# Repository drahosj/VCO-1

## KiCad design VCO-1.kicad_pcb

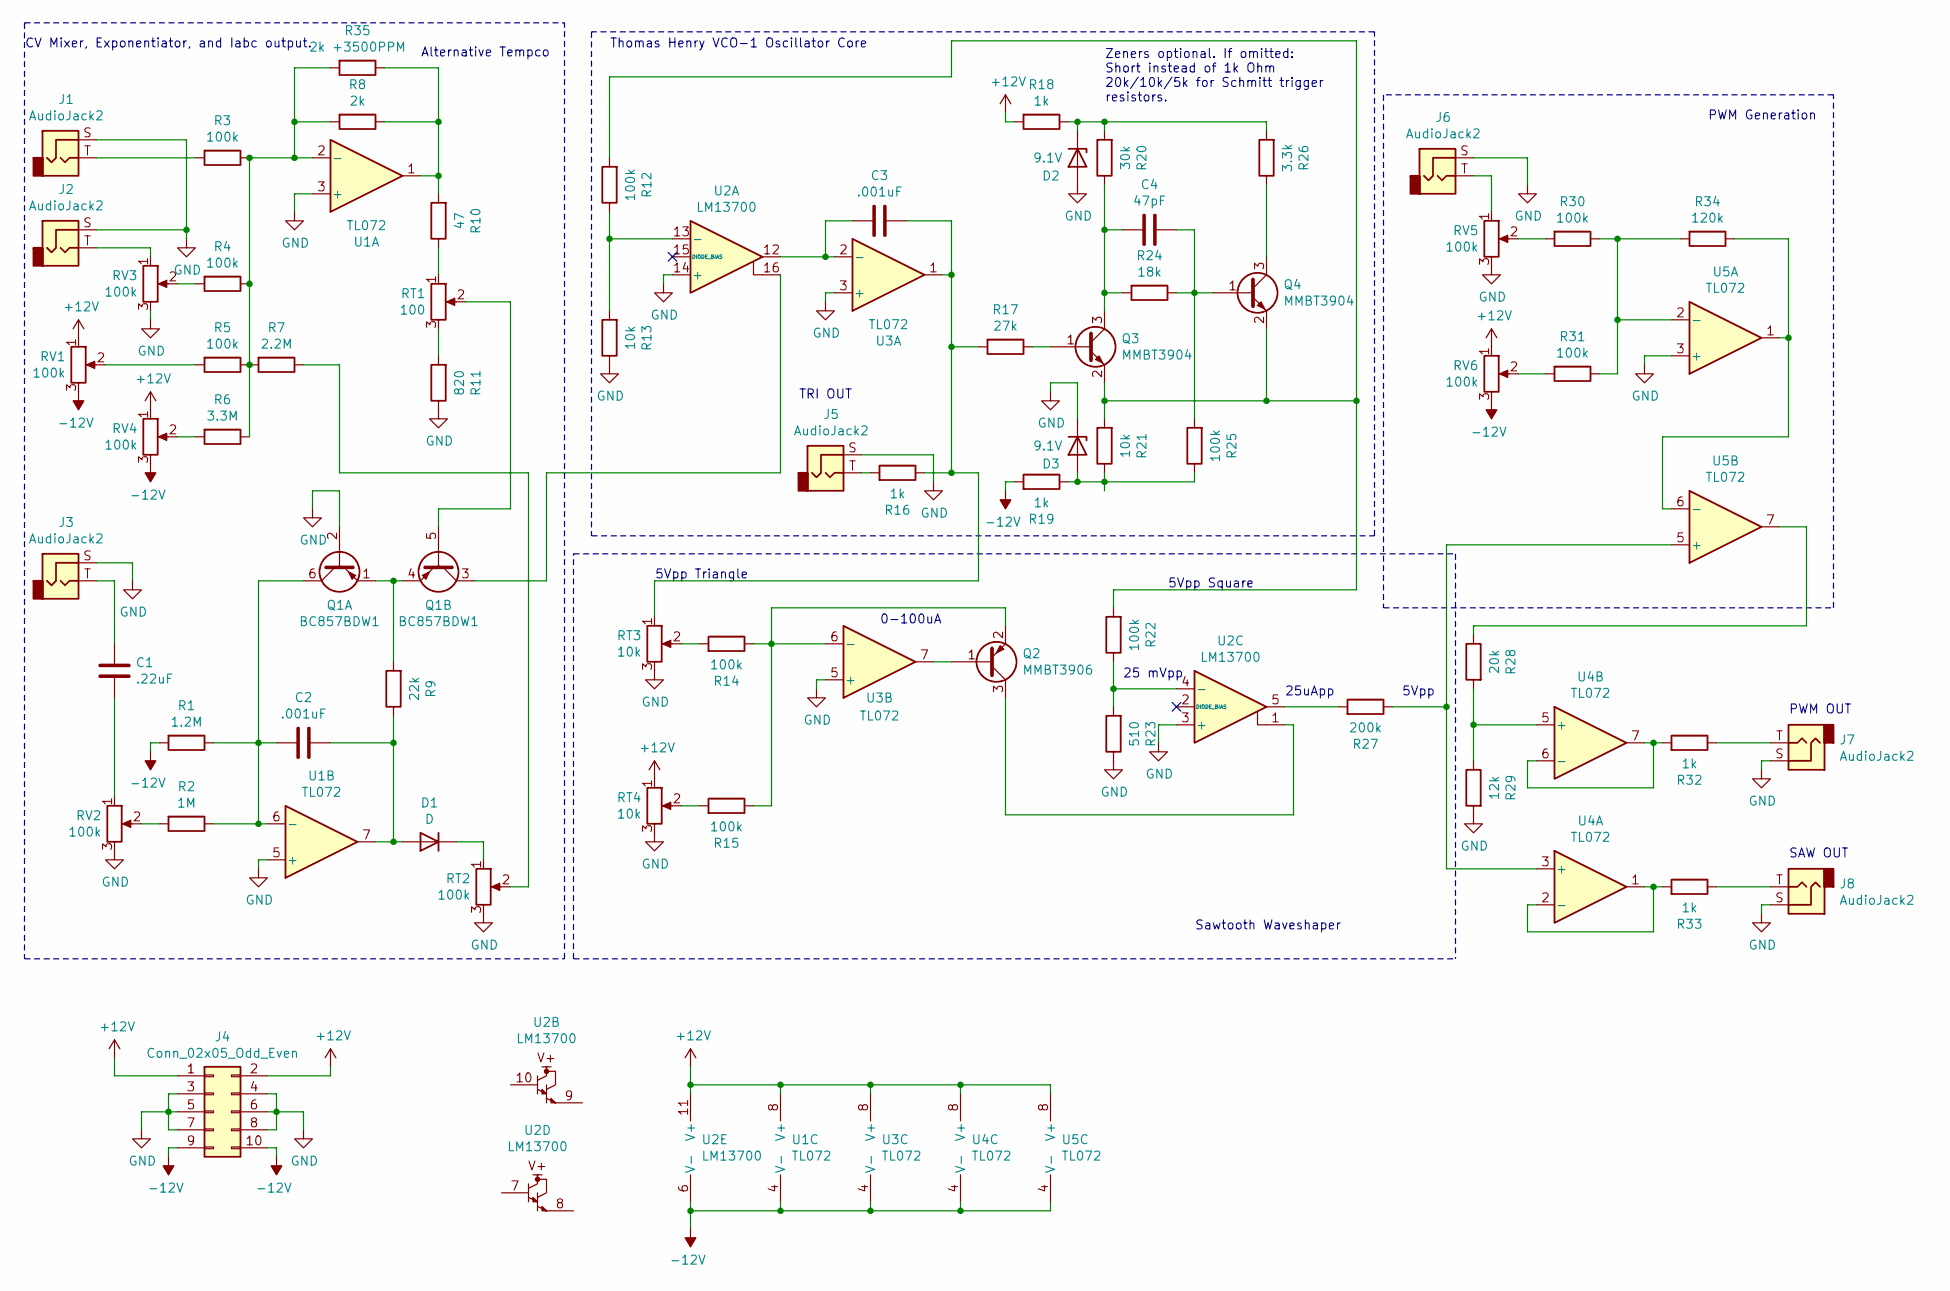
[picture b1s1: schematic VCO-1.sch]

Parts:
C1: .22uF; C_Rect_L10.3mm_W5.0mm_P7.50mm_MKS4
C2, C3: .001uF; C_Rect_L7.0mm_W4.5mm_P5.00mm
C4: 47pF; C_Rect_L4.0mm_W2.5mm_P2.50mm
D1: D; D_T-1_P5.08mm_Horizontal
D2, D3: 9.1V; D_DO-35_SOD27_P7.62mm_Horizontal
J1, J2, J3, J5, J6, J7, J8: AudioJack2; Jack_3.5mm_QingPu_WQP-PJ398SM_Vertical_CircularHoles
J4: Conn_02x05_Odd_Even; PinHeader_2x05_P2.54mm_Vertical
Q1: BC857BDW1; SOT-363_SC-70-6
Q2: MMBT3906; SOT-23
Q3, Q4: MMBT3904; SOT-23
R1: 1.2M; R_0805_2012Metric_Pad1.20x1.40mm_HandSolder
R2: 1M; R_0805_2012Metric_Pad1.20x1.40mm_HandSolder
R3, R4, R5, R12, R14, R15, R22, R25, R30, R31: 100k; R_0805_2012Metric_Pad1.20x1.40mm_HandSolder
R6: 3.3M; R_0805_2012Metric_Pad1.20x1.40mm_HandSolder
R7: 2.2M; R_0805_2012Metric_Pad1.20x1.40mm_HandSolder
R8: 2k; R_0805_2012Metric_Pad1.20x1.40mm_HandSolder
R9: 22k; R_0805_2012Metric_Pad1.20x1.40mm_HandSolder
R10: 47; R_0805_2012Metric_Pad1.20x1.40mm_HandSolder
R11: 820; R_0805_2012Metric_Pad1.20x1.40mm_HandSolder
R13, R21: 10k; R_0805_2012Metric_Pad1.20x1.40mm_HandSolder
R16, R18, R19, R32, R33: 1k; R_0805_2012Metric_Pad1.20x1.40mm_HandSolder
R17: 27k; R_0805_2012Metric_Pad1.20x1.40mm_HandSolder
R20: 30k; R_0805_2012Metric_Pad1.20x1.40mm_HandSolder
R23: 510; R_0805_2012Metric_Pad1.20x1.40mm_HandSolder
R24: 18k; R_0805_2012Metric_Pad1.20x1.40mm_HandSolder
R26: 3.3k; R_0805_2012Metric_Pad1.20x1.40mm_HandSolder
R27: 200k; R_0805_2012Metric_Pad1.20x1.40mm_HandSolder
R28: 20k; R_0805_2012Metric_Pad1.20x1.40mm_HandSolder
R29: 12k; R_0805_2012Metric_Pad1.20x1.40mm_HandSolder
R34: 120k; R_0805_2012Metric_Pad1.20x1.40mm_HandSolder
R35: 2k +3500PPM; R_Axial_DIN0414_L11.9mm_D4.5mm_P15.24mm_Horizontal
RT1: 100; Potentiometer_Bourns_3299W_Vertical
RT2: 100k; Potentiometer_Bourns_3299W_Vertical
RT3, RT4: 10k; Potentiometer_Bourns_3299W_Vertical
RV1, RV2, RV3, RV4, RV5, RV6: 100k; Potentiometer_Alpha_RD901F-40-00D_Single_Vertical_CircularH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
U1, U3, U4, U5: TL072; SOIC-8_3.9x4.9mm_P1.27mm
U2: LM13700; SOIC-16_3.9x9.9mm_P1.27mm

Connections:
+12V: J4.1, J4.2, R18.2, RT4.1, RV1.1, RV4.1, RV6.1, U1.8 (V+), U2.11 (V+), U3.8 (V+), U4.8 (V+), U5.8 (V+)
-12V: J4.9, J4.10, R1.2, R19.2, RV1.3, RV4.3, RV6.3, U1.4 (V-), U2.6 (V-), U3.4 (V-), U4.4 (V-), U5.4 (V-)
GND: D2.2 (A), D3.1 (K), J1.S, J2.S, J3.S, J4.3, J4.4, J4.5, J4.6, J4.7, J4.8, J5.S, J6.S, J7.S, J8.S, Q1.2 (B1), R11.1, R13.1, R23.1, R29.2, RT2.3, RT3.3, RT4.3, RV2.3, RV3.3, RV5.3, U1.3 (+), U1.5 (+), U2.3 (+), U2.14 (+), U3.3 (+), U3.5 (+), U5.3 (+)
unnamed: C1.1, J3.T
unnamed: C1.2, RV2.1
unnamed: C2.1, D1.2 (A), R9.1, U1.7
unnamed: C2.2, Q1.6 (C1), R1.1, R2.1, U1.6 (-)
unnamed: C3.1, R16.1, R17.2, RT3.1, U3.1
unnamed: C3.2, U2.12, U3.2 (-)
unnamed: C4.1, Q4.1 (B), R24.1, R25.2
unnamed: C4.2, Q3.3 (C), R20.1, R24.2
unnamed: D1.1 (K), RT2.1
unnamed: D2.1 (K), R18.1, R20.2, R26.2
unnamed: D3.2 (A), R19.1, R21.1, R25.1
unnamed: J1.T, R3.2
unnamed: J2.T, RV3.1
unnamed: J5.T, R16.2
unnamed: J6.T, RV5.1
unnamed: J7.T, R32.1
unnamed: J8.T, R33.1
unnamed: Q1.1 (E1), Q1.4 (E2), R9.2
unnamed: Q1.3 (C2), U2.16
unnamed: Q1.5 (B2), RT1.2
unnamed: Q2.1 (B), U3.7
unnamed: Q2.2 (E), R14.1, R15.1, U3.6 (-)
unnamed: Q2.3 (C), U2.1
unnamed: Q3.1 (B), R17.1
unnamed: Q3.2 (E), Q4.2 (E), R12.2, R21.2, R22.2
unnamed: Q4.3 (C), R26.1
unnamed: R2.2, RV2.2
unnamed: R3.1, R4.1, R5.1, R6.1, R7.2, R8.2, R35.2, U1.2 (-)
unnamed: R4.2, RV3.2
unnamed: R5.2, RV1.2
unnamed: R6.2, RV4.2
unnamed: R7.1, RT2.2
unnamed: R10.1, RT1.1
unnamed: R8.1, R10.2, R35.1, U1.1
unnamed: R11.2, RT1.3
unnamed: R12.1, R13.2, U2.13 (-)
unnamed: R14.2, RT3.2
unnamed: R15.2, RT4.2
unnamed: R22.1, R23.2, U2.4 (-)
unnamed: R27.1, U4.3 (+), U5.5 (+)
unnamed: R27.2, U2.5
unnamed: R28.1, U5.7
unnamed: R28.2, R29.1, U4.5 (+)
unnamed: R30.1, R31.1, R34.2, U5.2 (-)
unnamed: R30.2, RV5.2
unnamed: R31.2, RV6.2
unnamed: R32.2, U4.6 (-), U4.7
unnamed: R33.2, U4.1, U4.2 (-)
unnamed: R34.1, U5.1, U5.6 (-)

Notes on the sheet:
CV Mixer, Exponentiator, and Iabc output.
Thomas Henry VCO-1 Oscillator Core
Zeners optional. If omitted: Short instead of 1k Ohm 20k/10k/5k for Schmitt trigger resistors.
5Vpp Square
25 mVpp
5Vpp Triangle
0-100uA
25uApp
5Vpp
Sawtooth Waveshaper
PWM Generation
TRI OUT
PWM OUT
SAW OUT
Alternative Tempco

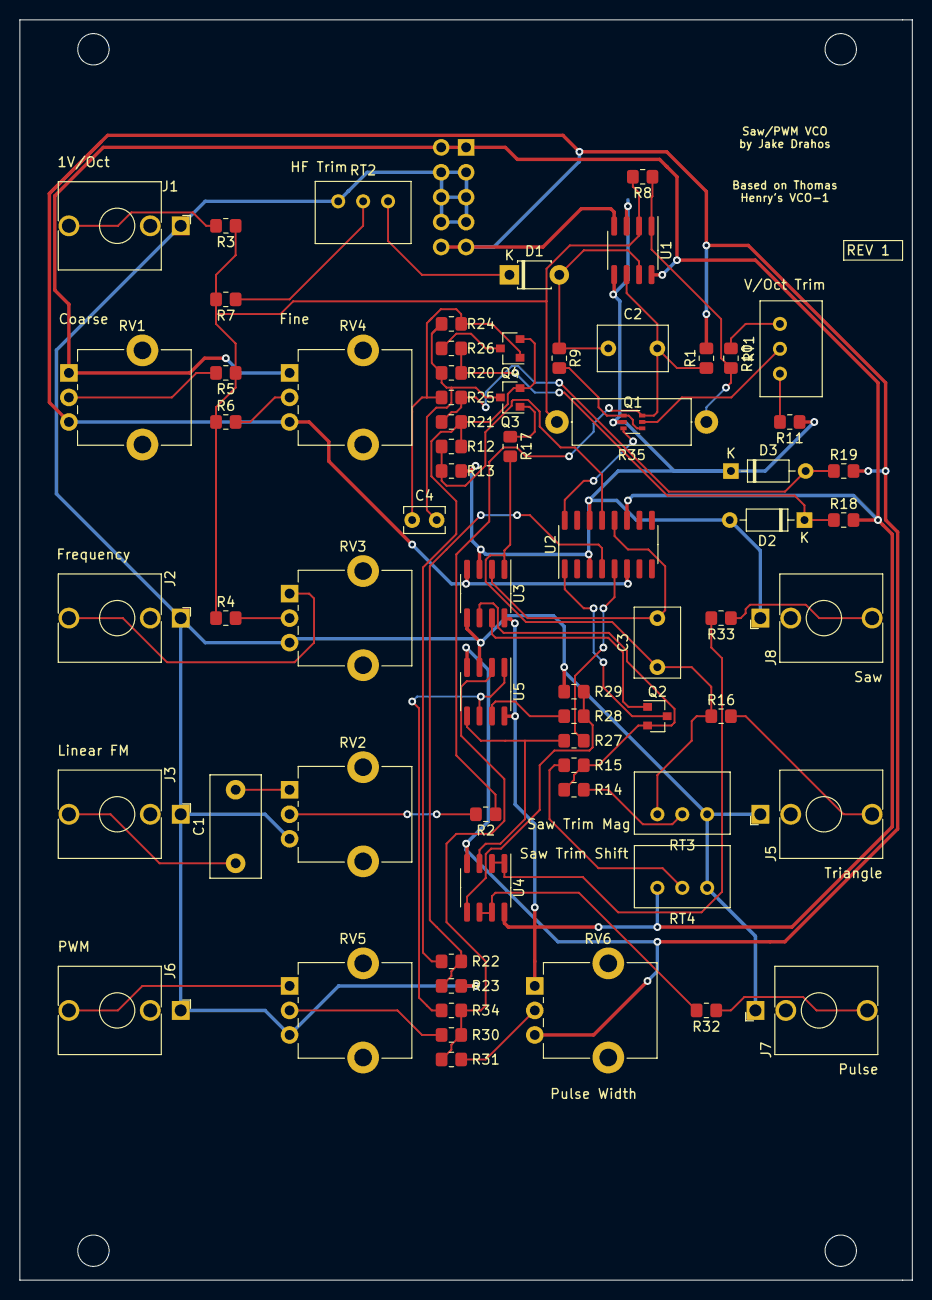
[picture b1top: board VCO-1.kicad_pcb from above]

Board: 2 copper layers, 91.0 x 128.5 mm, 69 parts (1 on the bottom side), 52 nets.

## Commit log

2021-01-12 Schematic done
2021-01-12 Added PDF
2021-01-12 Fixed missing input resistor for V/oct
2021-01-21 Board layed out
    Silkscreen done, should be good for fab.
2021-01-21 Fixed some silk screen
